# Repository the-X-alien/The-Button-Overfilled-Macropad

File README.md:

# Dhiaan's Button Overfilled Macropad

## The final product in Fusion 360

### My Schematic

I followed the Hackpad tutorial for the first version but after I figured out that 16 GPIO pins are too much I switched to a Matrix tutorial.
I followed the tutorial but instead of a 3x3 I made a 4x4.
The tutorial also explained how Anti-Ghosting worked so I also added diodes to incorperate the feature.

### My PCB

For the PCB I did it on my own besides the OLED display for which I took help from the Hackpad chat.

### The Case

*The cover is facing the wrong way

The case was the part I thought was the hardest but ended up becoming really easy from the Hackpad tutorial.
The only thing I had trouble with was finding out where to place the OLED on the top panel beacuse since we added 20 mm to each dimension.

### BOM

| Footprint          | Quantity | Supplier and ref       | Price                    |
|--------------------|----------|-------------------------|--------------------------|
| Cherry MX Switches | 16       | Hackclub                | Free                     |
| OLED Screen        | 1        | Hackclub                | Free                     |
| XIAO-RP2040-DIP    | 1        | Hackclub                | Free                     |
| Diodes             | 16       | Hackclub                | Free                     |
| Keycaps            | 16       | Hackclub                | Free                     |
| Case               | 1        | #Printing-Legion        | Free                     |
| PCB                | 5        | JLCPCB                  | $15 (with shipping and tax) |

### The Firmware

(This part is exactly the Firmware's README)

#### How I made it

I took the starter code from the Hackpad guide and used a tutorial to make it use a matrix instead.
Then I used ChatGPT to learn how to program the display.

#### What it does

The firmware makes the 4x4 Matrix into two parts. 
The top 3x4 is a numpad with 1-9 and the mulpitication and division function.
The bottom is a 4 key row where the 1st (leftmost) button types my whole email out,
the 2nd writes my school email out,
the 3nd writes my school password out,
and the 4th writes my home address which is very useful cause I always mess up on the 'Buellis' part

---

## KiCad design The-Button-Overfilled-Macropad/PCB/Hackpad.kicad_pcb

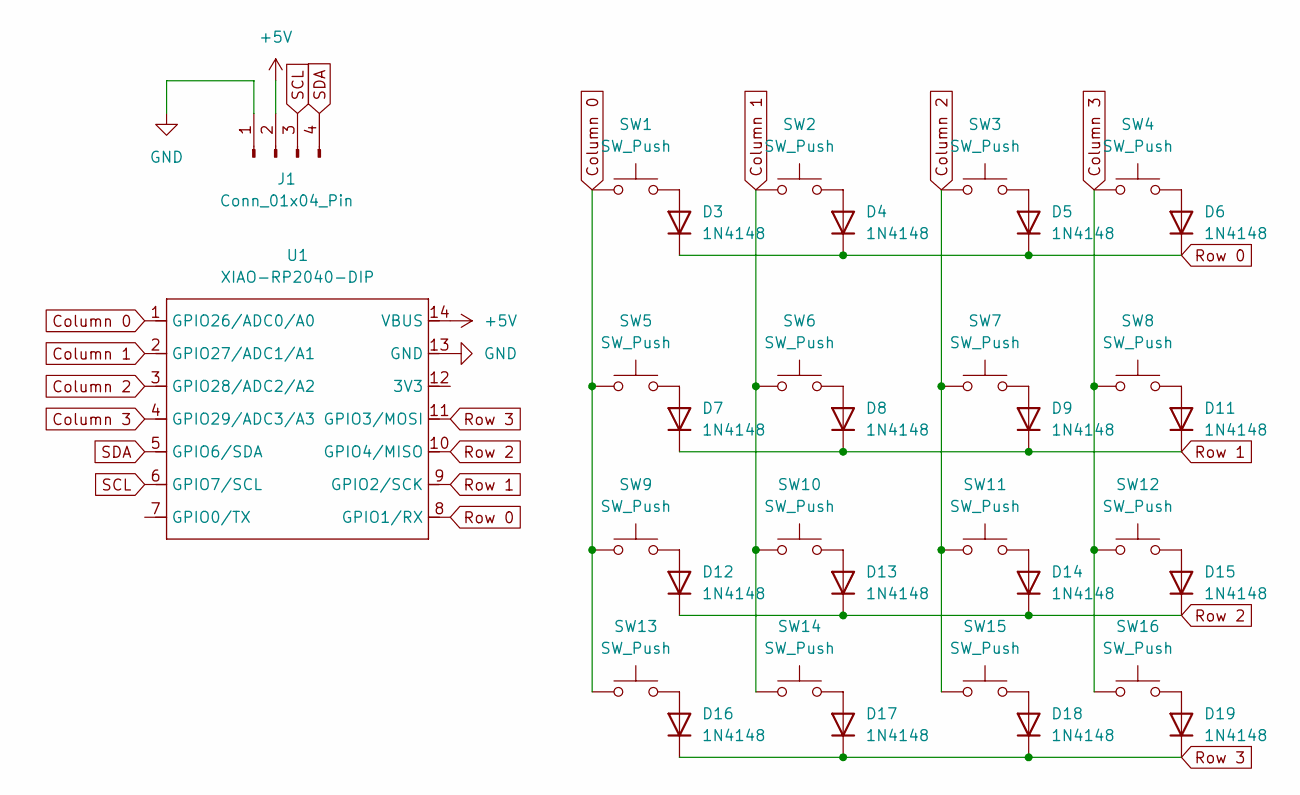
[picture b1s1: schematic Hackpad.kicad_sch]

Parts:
D3, D4, D5, D6, D7, D8, D9, D11, D12, D13, D14, D15, D16, D17, D18, D19: 1N4148; D_DO-35_SOD27_P7.62mm_Horizontal
J1: Conn_01x04_Pin; SSD1306-0.91-OLED-4pin-128x32
SW1, SW2, SW3, SW4, SW5, SW6, SW7, SW8, SW9, SW10, SW11, SW12, SW13, SW14, SW15, SW16: SW_Push; SW_Cherry_MX_1.00u_PCB
U1: XIAO-RP2040-DIP

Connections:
+5V: J1.2, U1.14 (VBUS)
Column 0: SW1.1, SW5.1, SW9.1, SW13.1, U1.1 (GPIO26/ADC0/A0)
Column 1: SW2.1, SW6.1, SW10.1, SW14.1, U1.2 (GPIO27/ADC1/A1)
Column 2: SW3.1, SW7.1, SW11.1, SW15.1, U1.3 (GPIO28/ADC2/A2)
Column 3: SW4.1, SW8.1, SW12.1, SW16.1, U1.4 (GPIO29/ADC3/A3)
GND: J1.1, U1.13 (GND)
unnamed: D3.2 (A), SW1.2
unnamed: D4.2 (A), SW2.2
unnamed: D5.2 (A), SW3.2
unnamed: D6.2 (A), SW4.2
unnamed: D7.2 (A), SW5.2
unnamed: D8.2 (A), SW6.2
unnamed: D9.2 (A), SW7.2
unnamed: D11.2 (A), SW8.2
unnamed: D12.2 (A), SW9.2
unnamed: D13.2 (A), SW10.2
unnamed: D14.2 (A), SW11.2
unnamed: D15.2 (A), SW12.2
unnamed: D16.2 (A), SW13.2
unnamed: D17.2 (A), SW14.2
unnamed: D18.2 (A), SW15.2
unnamed: D19.2 (A), SW16.2
Row 0: D3.1 (K), D4.1 (K), D5.1 (K), D6.1 (K), U1.8 (GPIO1/RX)
Row 1: D7.1 (K), D8.1 (K), D9.1 (K), D11.1 (K), U1.9 (GPIO2/SCK)
Row 2: D12.1 (K), D13.1 (K), D14.1 (K), D15.1 (K), U1.10 (GPIO4/MISO)
Row 3: D16.1 (K), D17.1 (K), D18.1 (K), D19.1 (K), U1.11 (GPIO3/MOSI)
SCL: J1.3, U1.6 (GPIO7/SCL)
SDA: J1.4, U1.5 (GPIO6/SDA)

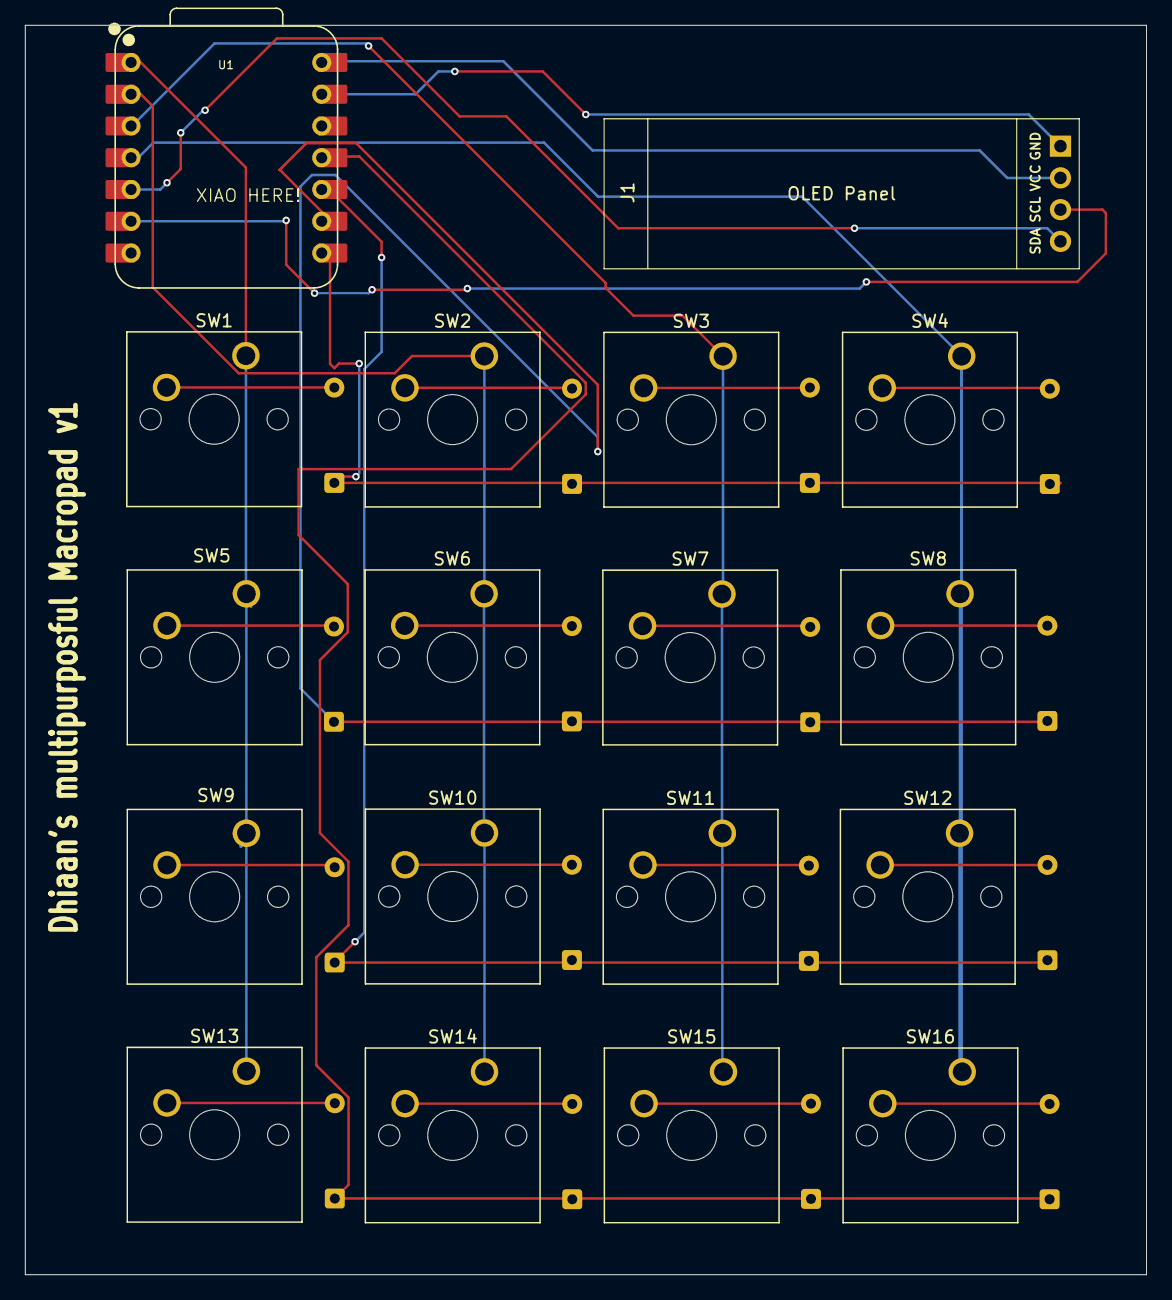
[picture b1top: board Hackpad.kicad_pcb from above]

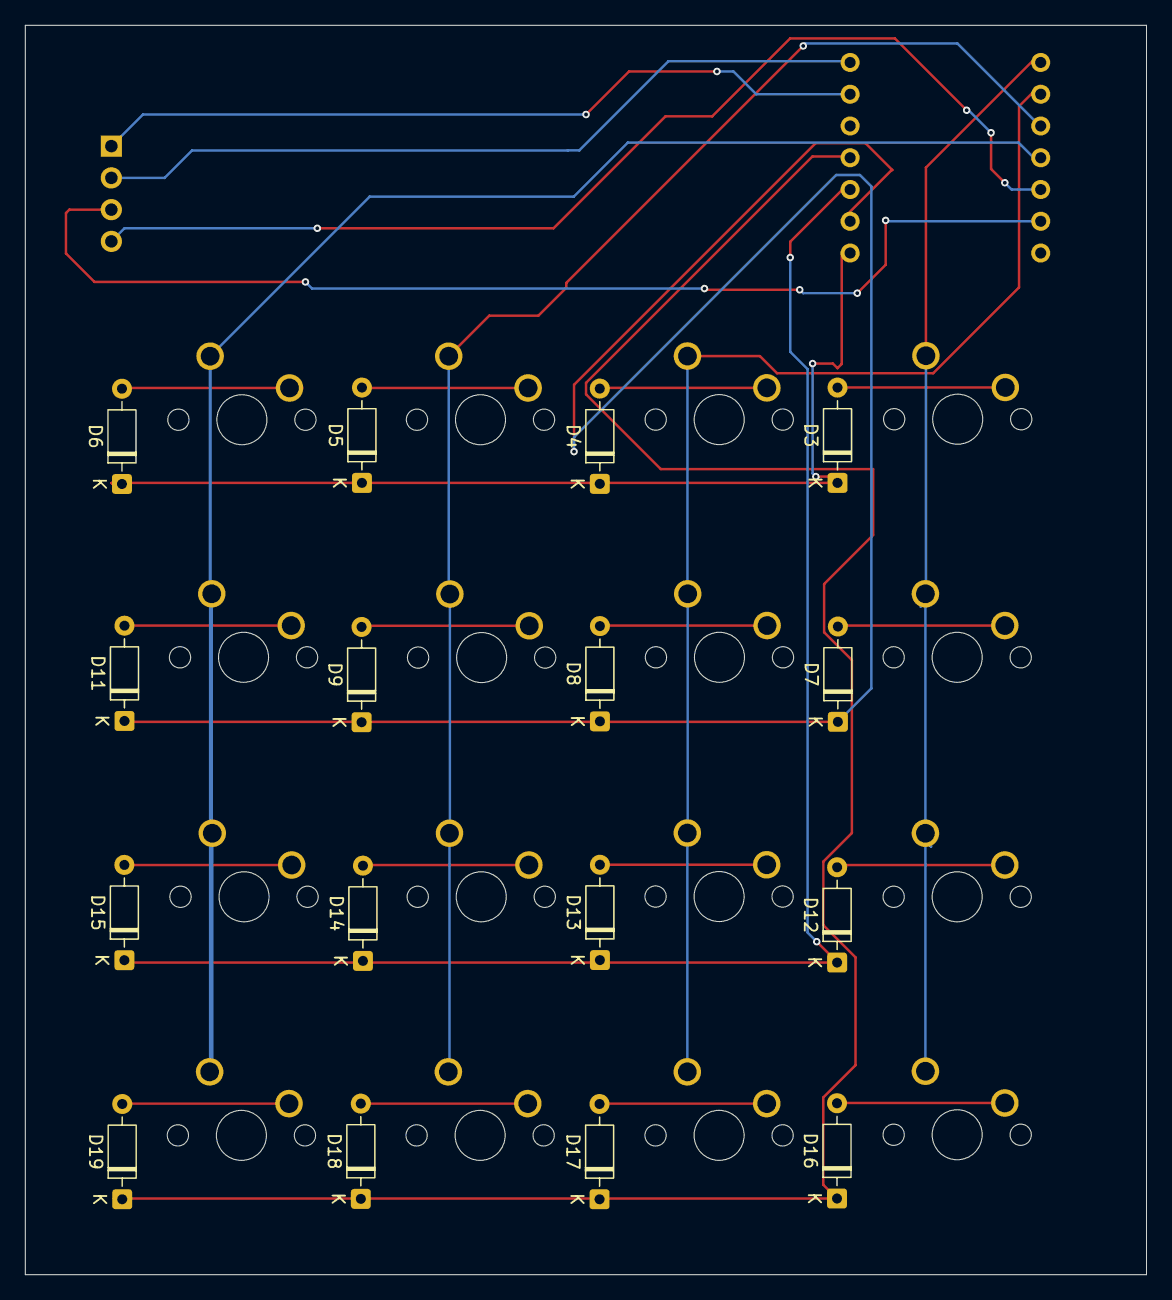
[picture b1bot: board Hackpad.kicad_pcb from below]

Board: 2 copper layers, 89.7 x 99.9 mm, 34 parts (16 on the bottom side), 28 nets.

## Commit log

2025-06-21 Create Production
2025-06-21 Create temp
2025-06-21 Create temp1
2025-06-21 Create temp2
2025-06-21 Create temp3
